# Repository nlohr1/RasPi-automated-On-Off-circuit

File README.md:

# RasPi-automated-On-Off-circuit
Automated safe shutdown of a Raspberry Pi single-board computer.

**Board with soldered components (52 x 28 mm)**  

This **automated** circuit acts in combination with a Python-Script (on the RasPi), shutting-off safely a Raspberry-Pi Single-Board-Computer.
Shut-off can be inizialized with a remote-controlled Switch (activated per WLAN) or with a Hardware-Button connecting one of the GPIO-Pins
of the RasPi to GND (=Ground).  
It provides the possibility to switch a concatenated Power-Relay on at startup (f.ex. to start a 3D-Printer) and a 2nd Button to manually
switch-on the 5V-Power for the RasPi (this switching "On" also the Printer-Power-Relais) and hold by the one of the GPIOs of the RasPi,
which on startup were switched high and on shutdown low.

This board is a modified copy of the work created from  
Hochschule München, FK 04, Prof. Jürgen Plate, http://www.netzmafia.de/skripten/hardware/RasPi/Projekt-OnOff/index.html

**Main attributes:**  
- integrated Schmitt-Trigger between Timing-Capacitor and Main-Switching-Mosfet,  
- detection of present Mains-Power through an optocoupler, activating the main Power-Relais (20A / 230VAC) for the machine/3D-Printer, because most
common available Remote-Switches can't **switch** safely more than a maximum of about 0,5 Amperes (~100W) - although they mostly are specified for "220V / 16A"
(= this beeing true only for the **uninterrupted** current...!).

Wiring of the System - schematic:
---------------------------------

Preliminary remarks
-------------------
A Computer booting from a File-System needs to have a built-in **save** shutdown before turning off his (main-)power.
The Raspberry Pi alas has no buit-in safe shutdown-program nor Shutdown-Button and normally will be directly "killed" powering off.  
This abrupt "Power-Off" is default use and mostly causes no problems. But if just at this "shut-off"-moment the system is writing to the file-system
(f.ex. to the SD-Card), this may result in a (boot-)file beeing unreadable or worse in a corrupted boot-sector - and probaby next time
the system can't boot anymore – the SD-Card (the booting-system) has to be set-up again... almost much work, which can be avoided
with an additional Python-Script + a safe Shutdwon-Circuit (Hardware like this) or a simple manual Button activating the Script.
The advantage of this Circuit is it shuts the whole Power off, keeping only the small 5V/2A-(USB)-Power-Supply in StandBy-Mode.

This Shutdwon-Box acts automatically: On startup it activates a Shutdown-Routine Script on the RasPi, waiting for the Signal (or Button)
to Power-Off. This Routine (a Python-Script) can be found on many places on the internet, but mostly it isn't activated automatically
but with a manual "Shut-down" Button. To automate this process the RasPi here gets his own 5V-Supply **beeing always on**, but 
shorted off inside the circuit, so that the RasPi (yet beeing in StandBy-Mode) now is completely off.

Shut-down Signal by absence of Main-Power
-----------------------------------------
If the Main-Power (f.ex. 230VAC or 24VDC for a 3D-Printer) is shut-off (per Main-Switch or Remote-Switch), this Circuit gets the missing
Power through an Optocoupler, which signals the Raspi to run the above mentionned shutdown-script before the Circuit switches the
5V-Power-line off after a waiting-time of about 30 seconds. After that only the small USB-Power-Supply rests "On", consuming only
a few mA sensing for presence of Main-Power, and if so, the (USB) 5V-Power-line is switched on again.

Design: Mains-Power (~230VAC) on the Optocoupler!
-------
!!! ATTENTION - DANGER: Mains Power or Voltages above 40V or currents above 30mA *flowing through human body* can cause mortal heart-paralysis,
even after minutes, hours or days after a shock ocurred! So be aware of what you do, specially:
1. NEVER touch the board manually beeing "On" with connected Mains-Power! Be cautious, put the circuit in a safe box and isolate every cable
with high-voltages!
2. In (hopeful never) the case of a shock: DONT STAY ALONE, visit a doctor IN ANY CASE - if your heart stands still and you are alone - this
beeing possible also after a longer time (!) - you are definitively dead!
3. You are warned, responsibility of what you are doing with the provided circuit + files here is on to you!

Function
--------
On StartUp the Shutdown-Script sets BCM-Pin-18 (WPi GPIO-1) as Output + HIGH to signal our On-Off-Board that the Raspi is up and running.
This Signal on the Board loads and holds the Timer-Capacitor on our Circuit permanently at "full-status" (+5V) during RasPi's active-time.  
Meanwhile the +Signal from Optocoupler (HIGH) is connected to RasPi's BCM-Pin-23 (WPi GPIO-4) and is constantly monitored on background.
If LOW it activates the Shutdown-script.
After the RasPi has run the Shutdown script and is savely "down" (= in StandBy-Mode, but yet not "off"), having disconnected (unmounted)
his file-system (shutdown-routine "sudo shutdwon -h now"), his main 5V-Power-Supply may also be switched off as above mentionned. (Note:
the RasPi blinks 10 times while going down, before beeing inactive / in StandBy-Mode).
After being "down" (at the end of the Shut-Down-Script), Pin-18 is switched LOW. This LOW-Signal on the Circuit goes through Dual-Mosfet
T2 to the Timer-Capacitor (C1), which now unloads through his parallel resistance (R4: 3,9MOhm). On about ~1/3 of Voltage (after ~30s)
the connected Schmitt-Trigger switches Mosfets T3 and T4 off and so the +5V-Power line is cut-off.  
Using here a Power-Mosfet (=T4) insted of a Relay has the advantage of consuming negligible current, beeing active as well as in waiting
(StandBy-)Mode.  
If more Switching-Power is necessary (for greater loads as a small RasPi), the P-Mosfet IRF7416 (10A/20mOhm) simply may be exchanged with
a stronger type, f.ex. a IRF8736 (18A/5mO) or IRF8788 (24A/3mO), having identical packages as the IRF7416, so possible exchange without 
layout-modification. (I choosed here the IRF7416 due to good availability, but also other compatible Mosfets may be used as well).

This automated "On-Off-Switch" can be used for all Raspberry-Pi versions or also PC-Boxes, consuming upto 4 Amps (or even more) on 5VDC.  

---------------------------------------------------------------------------------------------------------------------
Add-On: Reset-Button for the Pi
-------------------------------
If in someway the RasPi went into its StandBy-Mode, we need a (Hardware-)Reset-Button to wake it up. Since Pi's boards as yet misses
Reset Buttons, nevertheless on most boards we may find a prepared via named "Run", whitch is the Pin we are looking for as Reset-Pin.
Connecting this pin to "GND" (often located directly beside) – through a Push-Button, the Raspi comes up again and so the
whole periphery as Printer, etc.  

---------------------------------------------------------------------------------------------------------------------

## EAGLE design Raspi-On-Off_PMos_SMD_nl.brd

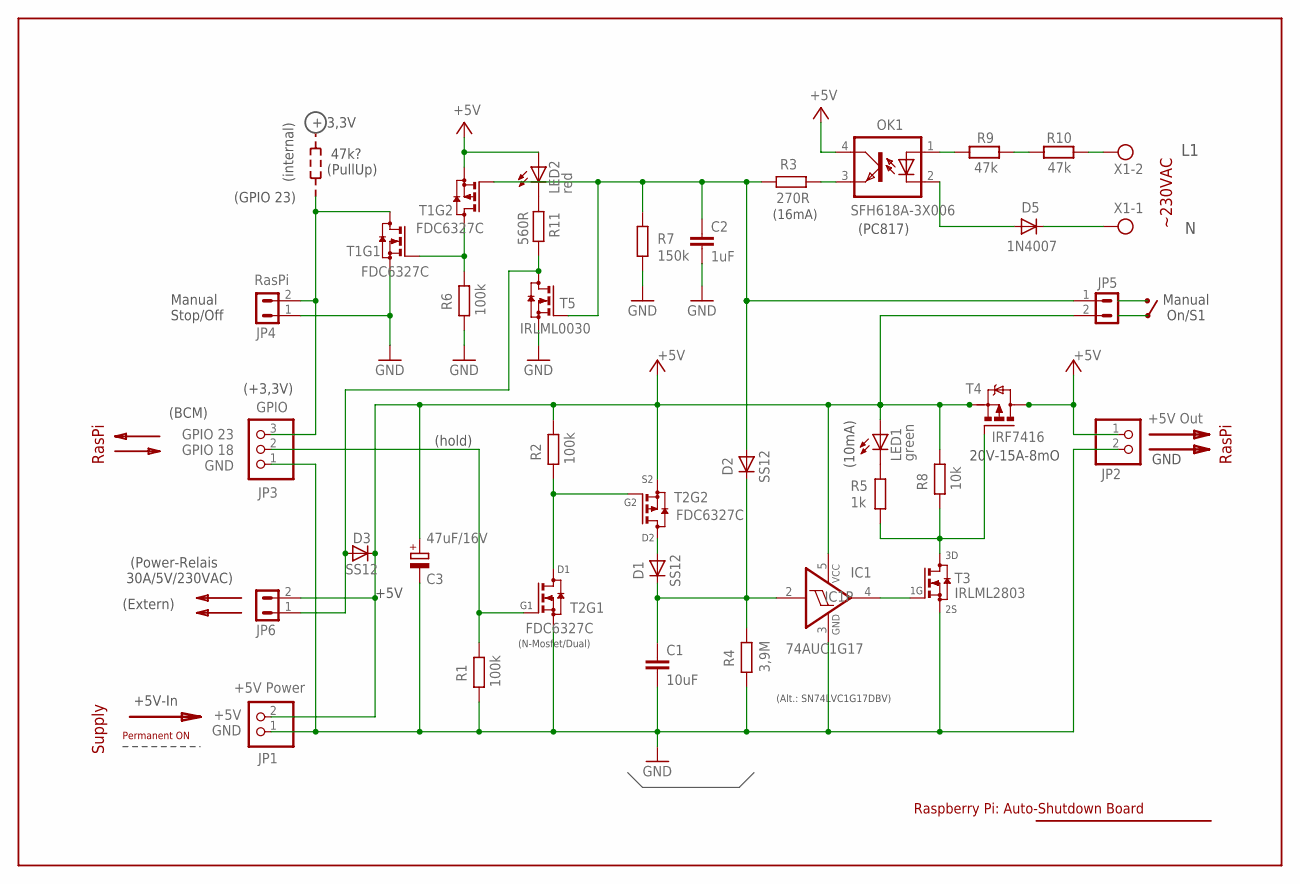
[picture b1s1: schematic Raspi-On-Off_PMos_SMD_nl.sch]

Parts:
C1: 10uF; C1206
C2: 1uF; C0805
C3: 47uF/16V; E2,5-6
D1, D2, D3: SS12; SOD123
D5: 1N4007; DO41-10
IC1: 74AUC1G17; SOT23-5
JP1: +5V Power; 1X02
JP2: RasPi; 1X02
JP3: GPIO; 1X03
JP4: RasPi; MA02-1R
JP5: On; MA02-1R
JP6: Relais; MA02-1R
LED1: green; LED3MM
LED2: red; LED3MM
OK1: SFH618A-3X006; DIP4-400
R1, R2, R6: 100k; R0805
R3: 270R; R0805
R4: 3,9M; R0805
R5: 1k; R0805
R7: 150k; R0805
R8: 10k; R0805
R11: 560R; R0805
T1, T2: FDC6327C; SOT23-6
T3: IRLML2803; SOT23
T4: IRF7416; SO-08
T5: IRLML0030; SOT23
X1: MKDSN1,5/2-5,08

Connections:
+5V: C3.+, D3.C, IC1.5 (VCC), JP1.2, JP5.2, JP6.2, LED1.A, LED2.A, OK1.4 (COL), R2.2, R8.2, T1.2 (S), T2.2 (S), T4.1 (S), T4.2 (S), T4.3 (S)
GND: C1.2, C2.2, C3.-, IC1.3 (GND), JP1.1, JP2.2, JP3.1, JP4.1, R1.1, R4.1, R6.1, R7.2, T1.5 (S), T2.5 (S), T3.2 (S), T5.2 (S)
unnamed: JP2.1, T4.5 (D), T4.6 (D), T4.7 (D), T4.8 (D)
unnamed: JP3.3, JP4.2, T1.6 (D)
unnamed: LED1.K (C), R5.2
unnamed: R5.1, R8.1, T3.3 (D), T4.4 (G)
unnamed: JP3.2, R1.2, T2.1 (G)
unnamed: D1.A, T2.4 (D)
unnamed: C1.1, D1.C, D2.C, IC1.2 (I), R4.2
unnamed: C2.1, D2.A, JP5.1, R3.1, R7.1, T1.3 (G), T5.1 (G)
unnamed: R2.1, T2.3 (G), T2.6 (D)
unnamed: OK1.3 (EMIT), R3.2
unnamed: R6.2, T1.1 (G), T1.4 (D)
unnamed: D5.A, OK1.2 (C)
unnamed: D5.C, X1.1
unnamed: D3.A, JP6.1, R11.1, T5.3 (D)
unnamed: LED2.K (C), R11.2
unnamed: IC1.4 (O), T3.1 (G)

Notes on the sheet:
+5V Out
+5V GND
GPIO 23 GPIO 18 GND
+5V-In
Raspberry Pi: Auto-Shutdown Board
(N-Mosfet/Dual)
(+3,3V)
Permanent ON
~230VAC
(BCM)
Manual Stop/Off
+ 3,3V
47k? (PullUp)
(internal)
(GPIO 23)
(PC817)
(hold)
20V-15A-8mO
(10mA)
(16mA)
(Power-Relais 30A/5V/230VAC)
(Extern)
(Alt.: SN74LVC1G17DBV)
RasPi
Supply
+5V
47k
R10
Manual On/S1
GND

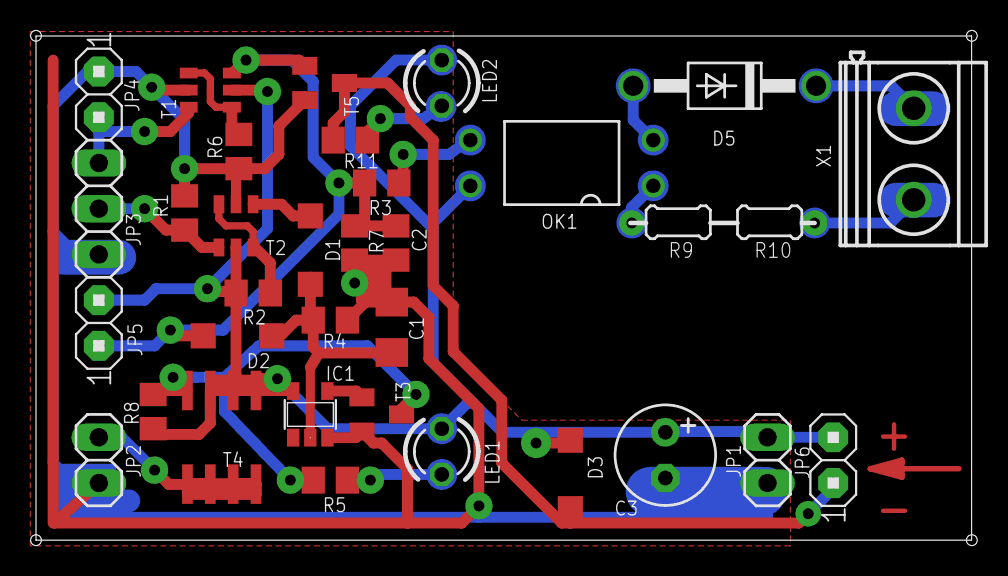
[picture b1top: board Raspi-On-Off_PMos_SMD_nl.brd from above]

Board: 2 copper layers, 52.0 x 28.0 mm, 32 parts (0 on the bottom side), 18 nets.
